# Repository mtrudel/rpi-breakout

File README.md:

# Raspberry Pi Breakout Board (v2)

A simple Raspberry Pi pHAT to break out common interfaces & GPIO, with
allowances for several common IO setups:

* Pinouts for I2C, UART, and 1-Wire (pullups included where needed)
* GPIO breakouts for pins 12, 13, 22, 23, 24, with the following options:
    * Simple 2-pin setup with GPIO & GND, suitable for input or adhoc use
    * LED driving setup with integrated resistor, suitable for smaller LEDs
    * Sink-side transistor network with integrated resistor for driving larger LEDs
    * Sink-side transistor network with 2-pin output (NPN collector & 5V rail)

All resistor footprints include allowance for either through-hole or 0805 SMD
mounting.

Available at [OSH Park](https://oshpark.com/shared_projects/bwpZYGX8).

The board provides the following interfaces:

## 40 Pin Duplicate

The [40 pin header](https://pinout.xyz) is duplicated pin-for-pin; use this for one-off access to pins as needed.

## I2C

Breaks out the RPi's primary [I2C](https://pinout.xyz/pinout/i2c) interface (ie: not the EEPROM interface). Pinout is (from left to right looking at the top of the board):

* Pin 1: 3.3V
* Pin 2: I2C Data (RPi BCM2)
* Pin 3: I2C Clock (RPi BCM3)
* Pin 4: Ground

## UART

Breaks out the RPi's [UART](https://pinout.xyz/pinout/uart). Pinout is (from left to right looking at the top of the board):

* Pin 1: 3.3V
* Pin 2: Tx (RPi BCM14)
* Pin 3: Rx (RPi BCM15)
* Pin 4: Ground

## 1-Wire

Breaks out the RPi's [1-Wire](https://pinout.xyz/pinout/1_wire) interface. Pinout is (from left to right looking at the top of the board):

* Pin 1: 3.3V
* Pin 2: Data (RPi BCM4)
* Pin 3: Ground

The 1-Wire spec mandates a 4.7k pullup resistor on the data line; this can be
done by populating the resistor below the 1-wire header (there is provision to
install either a through hole resistor or an 0805 SMD; both connections are
wired in parallel)

## GPIO

Five GPIOs are broken out, corresponding to BCM12-BCM13 and BCM22-BCM24. The pinout for each is as follows (looking at the top of the board):

```
              o||o <-------- <-- Collector current limiting resistor
              |            |
              1  2 <-- 5V  |
              |            |
              3  4 <--------

   ---------> 5  6 <-- GPIO
   |             |
   |  GND --> 7  8 <-- GPIO
   |             |
   ---------> o||o <-- GPIO current limiting resistor
```

* Pin 1: Transistor collector output. Common with pin 3
* Pin 2: 5V (**Note this is 5V**)
* Pin 3: Transistor collector output. Common with pin 1
* Pin 4: Resistor terminal (for upper resistor)
* Pin 5: Resistor terminal (for lower resistor)
* Pin 6: GPIO pin (corresponds to BCMXX). Common with pin 8
* Pin 7: Ground
* Pin 8: GPIO pin (corresponds to BCMXX). Common with pin 6

There are two resistors in each GPIO network. The upper resistor is wired to pin
4 on one end and pins 1&3 on the other. It is intended as a current limiting
resistor when a transistor is used to drive a large LED. The lower resistor is
wired to pins 5 on one end and 6&8 on the other. It is intended as a current
limiting resistor when driving a small LED or a switching transistor directly
from the GPIO pin. Both resistor footprints include allowance for either
through-hole or 0805 SMD mounting.

Pin 6 is always unpopulated and exposes the GPIO directly. This is useful for
probing during development.

This layout looks a bit odd but allows each pin to be conveniently used in a
variety of ways. See below for instructions on how to wire up each mode; I
promise this will make sense once you use it.

### Using a GPIO as an input

1. Wire your sensor between pins 7 and 8 of the relevant GPIO column, and set
   the GPIO to use a pullup resistor in software.
2. The GPIO will be high when the sensor is open, and go low when the sensor
   closes.

In pictures:

```
   1  2

   3  4

   5  6

   7  8
   |  |
   |__|  <-- switch
```

### Driving a small LED

This comes with the usual caveats about driving LEDs directly off GPIO pins; so
long as you're driving small LEDs in a non-continuous manner you should be fine,
but caveat emptor etc.

1. Wire an appropriate resistor (~ 330Ω) in the lower resistor position of the
   relevant GPIO column (there is provision to install either a through hole
   resistor or an 0805 SMD; both connections are wired in parallel).
2. Wire your LED with the anode (longer leg) in pin 5 and the cathode (shorter
   leg) in pin 7.
3. You can now turn the LED on by driving the relevant GPIO output high.

In pictures:

```
                      1  2

                      3  4

           /|-------- 5  6
 LED ->   | |
           \|-----    7  8

 ~330Ω resistor ->    o||o
```

### Driving a large LED with a transistor

1. Wire an appropriate resistor (~ 100Ω) in the lower resistor position of the
   relevant GPIO column (there is provision to install either a through hole
   resistor or an 0805 SMD; both connections are wired in parallel). This resistor
   will be wired between the GPIO output and transistor base and serves to limit
   the current (sourced from the GPIO pin) that will drive the base of the
   transistor.
2. Wire an NPN transistor such as a 2N2222 with the emitter in pin 7, the base
   in pin 5, and the collector in pin 3. For the common D-shaped 2N2222
   packaging, this will correspond to the flat side being to the right
3. Wire an appropriate resistor (exact value will depend on what kind of LED
   you're driving; **NOTE that pin 2 supplies 5V**) in the upper resistor
   position of the relevant GPIO column (there is provision to install either a
   through hole resistor or an 0805 SMD; both connections are wired in parallel).
   This resistor will be wired serves to limit the current into the LED.
4. Wire your LED with the anode (longer leg) in pin 2 and the cathode (shorter
   leg) in pin 4.

In pictures:

```
  LED resistor   ->    o||o

                       1  2 ---------|\
                                     | | <-- LED
            /|C------  3  4    ------|/
           / |
2N2222 -> |  |B------  5  6
           \ |
            \|E------  7  8

  ~100Ω resistor ->    o||o
```

### Driving an external load with a transistor

This is pretty similar to the previous case of driving a larger LED, but
accesses the switching transistor's collector directly. This comes with the
usual caveats about transistor / sink sizing etc. It's assumed that you know
what you're doing in this scenario.

1. Wire an appropriate resistor (~ 100Ω) in the lower resistor position of the
   relevant GPIO column (there is provision to install either a through hole
   resistor or an 0805 SMD; both connections are wired in parallel). This resistor
   will be wired between the GPIO output and transistor base and serves to limit
   the current (sourced from the GPIO pin) that will drive the base of the
   transistor.
2. Wire an NPN transistor such as a 2N2222 with the emitter in pin 7, the base
   in pin 5, and the collector in pin 3. For the common D-shaped 2N2222
   packaging, this will correspond to the flat side being to the right.
3. Wire your load to pin 1. If useful to your situation, you can also access 5V
   via pin 2 as needed

In pictures:

```
              Load --> 1  2 <-- 5V if needed

            /|C------  3  4
           / |
2N2222 -> |  |B------  5  6
           \ |
            \|E------  7  8

  ~100Ω resistor ->    o||o
```

# License

MIT

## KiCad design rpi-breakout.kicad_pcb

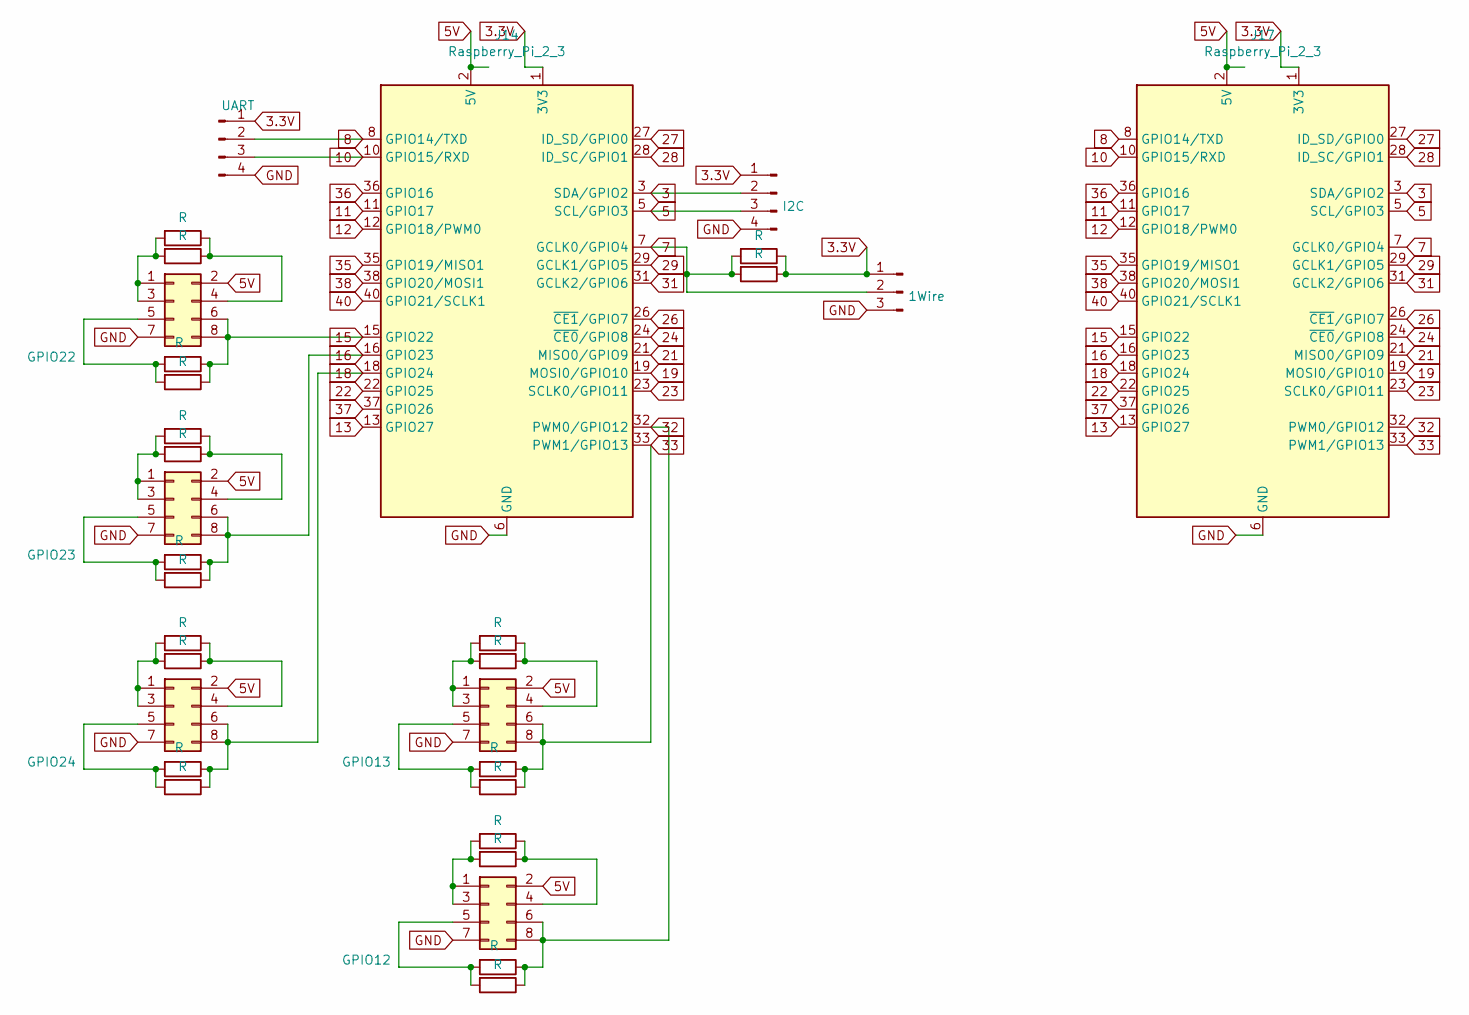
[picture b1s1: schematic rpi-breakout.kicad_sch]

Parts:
GPIO12: GPIO12; PinHeader_2x04_P2.54mm_Vertical
GPIO13: GPIO13; PinHeader_2x04_P2.54mm_Vertical
GPIO22: GPIO22; PinHeader_2x04_P2.54mm_Vertical
GPIO23: GPIO23; PinHeader_2x04_P2.54mm_Vertical
GPIO24: GPIO24; PinHeader_2x04_P2.54mm_Vertical
J13: UART; PinHeader_1x04_P2.54mm_Vertical
J14, J17: Raspberry_Pi_2_3; PinHeader_2x20_P2.54mm_Vertical
J15: I2C; PinHeader_1x04_P2.54mm_Vertical
J16: 1Wire; PinHeader_1x03_P2.54mm_Vertical
R7, R9, R10, R14, R15, R18, R19, R22, R23, R26, R27: R; R_0805_2012Metric_Pad1.20x1.40mm_HandSolder
R8, R11, R12, R13, R16, R17, R20, R21, R24, R25, R28: R; R_Axial_DIN0204_L3.6mm_D1.6mm_P5.08mm_Horizontal

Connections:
3: J14.3 (SDA/GPIO2), J15.2, J17.3 (SDA/GPIO2)
3.3V: J13.1, J14.1 (3V3), J14.17 (3V3), J15.1, J16.1, J17.1 (3V3), J17.17 (3V3), R7.1, R8.1
5: J14.5 (SCL/GPIO3), J15.3, J17.5 (SCL/GPIO3)
5V: GPIO12.2, GPIO13.2, GPIO22.2, GPIO23.2, GPIO24.2, J14.2 (5V), J14.4 (5V), J17.2 (5V), J17.4 (5V)
7: J14.7 (GCLK0/GPIO4), J16.2, J17.7 (GCLK0/GPIO4), R7.2, R8.2
8: J13.2, J14.8 (GPIO14/TXD), J17.8 (GPIO14/TXD)
10: J13.3, J14.10 (GPIO15/RXD), J17.10 (GPIO15/RXD)
11: J14.11 (GPIO17), J17.11 (GPIO17)
12: J14.12 (GPIO18/PWM0), J17.12 (GPIO18/PWM0)
13: J14.13 (GPIO27), J17.13 (GPIO27)
15: GPIO22.6, GPIO22.8, J14.15 (GPIO22), J17.15 (GPIO22), R19.1, R20.1
16: GPIO23.6, GPIO23.8, J14.16 (GPIO23), J17.16 (GPIO23), R15.1, R16.1
18: GPIO24.6, GPIO24.8, J14.18 (GPIO24), J17.18 (GPIO24), R27.1, R28.1
19: J14.19 (MOSI0/GPIO10), J17.19 (MOSI0/GPIO10)
21: J14.21 (MISO0/GPIO9), J17.21 (MISO0/GPIO9)
22: J14.22 (GPIO25), J17.22 (GPIO25)
23: J14.23 (SCLK0/GPIO11), J17.23 (SCLK0/GPIO11)
24: J14.24 (~CE0/GPIO8), J17.24 (~CE0/GPIO8)
26: J14.26 (~CE1/GPIO7), J17.26 (~CE1/GPIO7)
27: J14.27 (ID_SD/GPIO0), J17.27 (ID_SD/GPIO0)
28: J14.28 (ID_SC/GPIO1), J17.28 (ID_SC/GPIO1)
29: J14.29 (GCLK1/GPIO5), J17.29 (GCLK1/GPIO5)
31: J14.31 (GCLK2/GPIO6), J17.31 (GCLK2/GPIO6)
32: GPIO12.6, GPIO12.8, J14.32 (PWM0/GPIO12), J17.32 (PWM0/GPIO12), R23.1, R24.1
33: GPIO13.6, GPIO13.8, J14.33 (PWM1/GPIO13), J17.33 (PWM1/GPIO13), R9.1, R12.1
35: J14.35 (GPIO19/MISO1), J17.35 (GPIO19/MISO1)
36: J14.36 (GPIO16), J17.36 (GPIO16)
37: J14.37 (GPIO26), J17.37 (GPIO26)
38: J14.38 (GPIO20/MOSI1), J17.38 (GPIO20/MOSI1)
40: J14.40 (GPIO21/SCLK1), J17.40 (GPIO21/SCLK1)
GND: GPIO12.7, GPIO13.7, GPIO22.7, GPIO23.7, GPIO24.7, J13.4, J14.6 (GND), J14.9 (GND), J14.14 (GND), J14.20 (GND), J14.25 (GND), J14.30 (GND), J14.34 (GND), J14.39 (GND), J15.4, J16.3, J17.6 (GND), J17.9 (GND), J17.14 (GND), J17.20 (GND), J17.25 (GND), J17.30 (GND), J17.34 (GND), J17.39 (GND)
unnamed: GPIO12.1, GPIO12.3, R21.2, R22.2
unnamed: GPIO12.4, R21.1, R22.1
unnamed: GPIO12.5, R23.2, R24.2
unnamed: GPIO13.1, GPIO13.3, R10.2, R11.2
unnamed: GPIO13.4, R10.1, R11.1
unnamed: GPIO13.5, R9.2, R12.2
unnamed: GPIO22.1, GPIO22.3, R17.2, R18.2
unnamed: GPIO22.4, R17.1, R18.1
unnamed: GPIO22.5, R19.2, R20.2
unnamed: GPIO23.1, GPIO23.3, R13.2, R14.2
unnamed: GPIO23.4, R13.1, R14.1
unnamed: GPIO23.5, R15.2, R16.2
unnamed: GPIO24.1, GPIO24.3, R25.2, R26.2
unnamed: GPIO24.4, R25.1, R26.1
unnamed: GPIO24.5, R27.2, R28.2

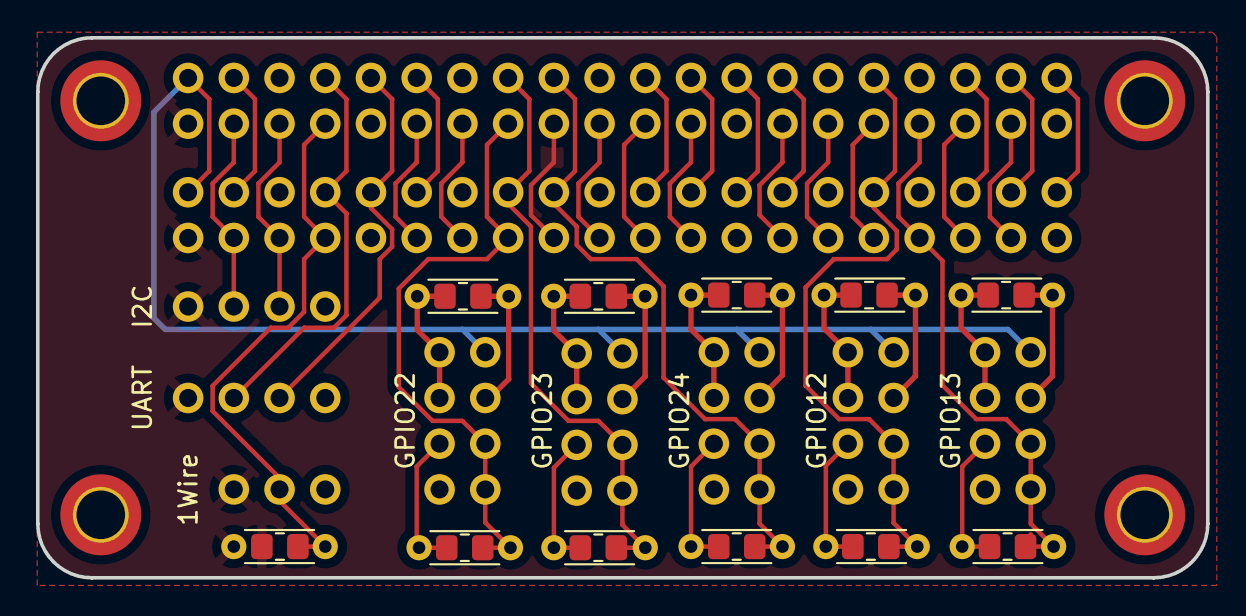
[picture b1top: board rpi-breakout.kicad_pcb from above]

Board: 2 copper layers, 65.0 x 30.0 mm, 32 parts (0 on the bottom side), 46 nets.

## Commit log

2019-03-11 Update README.md formatting
2019-03-30 Fix corner mounting holes, increase spacing b/w headers. Tag 1.1
2019-04-01 Fix mossing renames from rpi_breakout to rpi-breakout
2019-04-01 v2.0: Add 2 more GPIOs, re-layout on 100 mil grid
2026-02-07 Second pass at v2.0 (previous was unshipped)
